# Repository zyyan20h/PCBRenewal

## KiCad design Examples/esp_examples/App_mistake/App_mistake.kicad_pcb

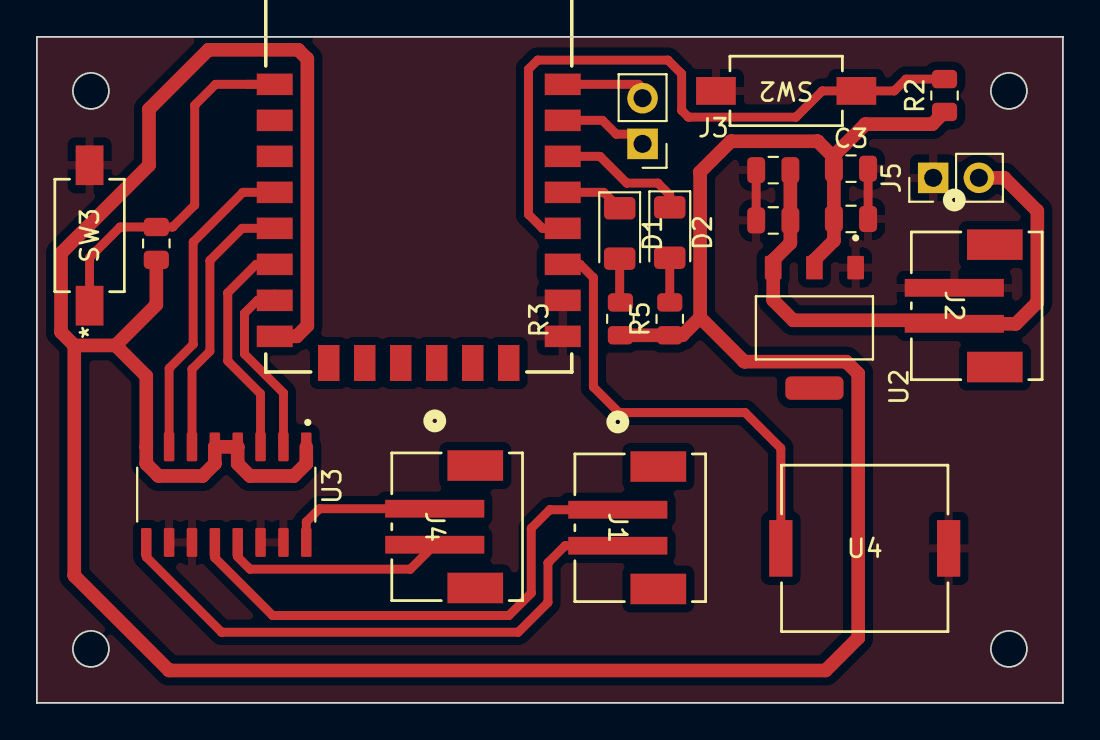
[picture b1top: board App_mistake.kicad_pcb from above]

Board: 2 copper layers, 57.0 x 37.0 mm, 21 parts (0 on the bottom side), 20 nets.

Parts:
C1, C2, C3, C4: C; C_0805_2012Metric
D1, D2: LED; LED_1206_3216Metric
J1, J2, J4: B2B-PH-SM4-TBLFSN; B2B-PH-SM4-TBLFSN_JST
J3, J5: Conn_01x02_Pin; PinHeader_1x02_P2.54mm_Vertical
R1, R2, R3, R5: R; R_0805_2012Metric
SW2, SW3: RS-282G05A3-SM RT; RS-282G05A3-SM RT_CNK
U1: ESP-12F
U2: AMS1117-3.3; SOT229P700X180-4N
U3: MX1508
U4: CPT-9019S-SMT-TR; SM_CPT_9X9_CUD

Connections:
/INL: J3.1, U1.21 (RXD)
/LED1: D1.1 (K), U1.19 (GPIO4)
/LED2: D2.1 (K), U1.20 (GPIO5)
/RST: R1.1, SW3.1, U1.1 (RST)
/VIN: C1.2, C2.2, J2.2, J5.2, U2.3 (VIN)
/boot: R2.2, SW2.1, U1.18 (GPIO0)
/buzzer: U1.17 (GPIO2), U4.1
/in1: U1.5 (GPIO14), U3.6 (INA2)
/in2: U1.4 (GPIO16), U3.7 (INB2)
/in3: U1.7 (GPIO13), U3.2 (INA1)
/in4: U1.6 (GPIO12), U3.3 (INB1)
GND: C1.1, C2.1, C3.2, C4.2, J2.1, J5.1, SW2.2, SW3.2, U1.15 (GND), U1.16 (GPIO15), U2.1 (GND/ADJ), U3.10 (AGND2), U3.11 (PGND2), U3.14 (AGND1), U3.15 (PGND1), U4.2
unnamed: D1.2 (A), R3.1
unnamed: D2.2 (A), R5.2
unnamed: J3.2, U1.22 (TXD)
unnamed: J4.1, U3.16 (OUTA1)
unnamed: J1.1, U3.12 (OUTA2)
unnamed: J4.2, U3.13 (OUTB1)
unnamed: J1.2, U3.9 (OUTB2)
VCC: C3.1, C4.1, R1.2, R2.1, R3.2, R5.1, U1.8 (VCC), U2.2 (VOUT), U3.1 (VCC1), U3.4 (VDD1), U3.5 (VCC2), U3.8 (VDD2)

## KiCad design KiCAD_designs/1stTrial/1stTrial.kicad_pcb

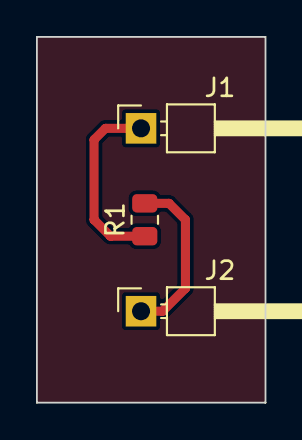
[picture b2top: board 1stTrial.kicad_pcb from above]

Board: 2 copper layers, 12.7 x 20.3 mm, 3 parts (0 on the bottom side), 2 nets.

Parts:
J1, J2: Conn_01x01_Pin; PinHeader_1x01_P2.54mm_Horizontal
R1: R; R_0805_2012Metric

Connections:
unnamed: J1.1, R1.1
unnamed: J2.1, R1.2

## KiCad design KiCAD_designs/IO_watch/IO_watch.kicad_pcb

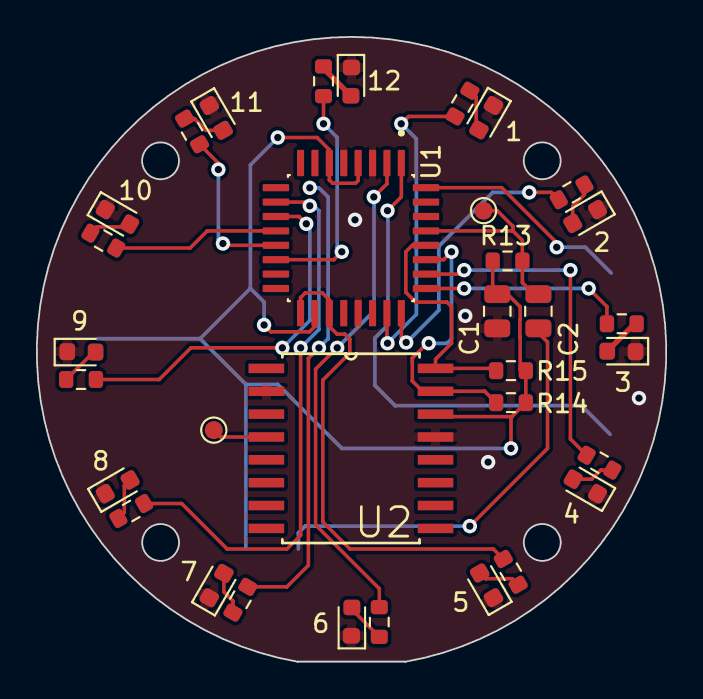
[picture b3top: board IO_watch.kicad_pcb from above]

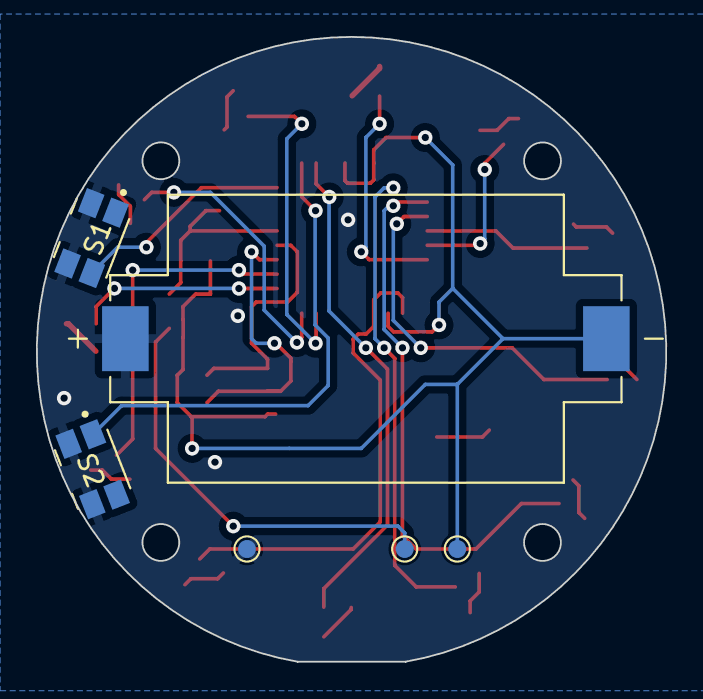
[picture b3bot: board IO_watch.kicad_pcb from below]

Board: 2 copper layers, 35.0 x 34.7 mm, 39 parts (6 on the bottom side), 33 nets.

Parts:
1, 2, 3, 4, 5, 12: LED; LED_0603_1608Metric
BT1: 1060TR; BAT_1060TR
C1: 1uF; C_0805_2012Metric
C2: 0.1uF; C_0805_2012Metric
D6, D7, D8, D9, D10, D11: LED; LED_0603_1608Metric
R1, R2, R3, R4, R5, R6, R7, R8, R9, R10, R11, R12: R; R_0603_1608Metric
R13, R14, R15: 10K; R_0603_1608Metric
S1, S2: EVQ-P7A01P; SW_EVQ-P7A01P
TP1, TP2, TP5, TP6, TP7: TestPoint; TestPoint_Pad_D1.0mm
U1: ATMEGA328P-AU; atmega328P_shinked
U2: DS3231S; DS3231

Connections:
/A0: R1.2, U1.23 (PC0)
/A1: R2.2, U1.24 (PC1)
/A2: R3.2, U1.25 (PC2)
/A3: R4.2, U1.26 (PC3)
/D2: S1.1_1, S1.1_2, U1.32 (PD2)
/D3: S2.1_1, S2.1_2, U1.1 (PD3)
/D4: R6.2, U1.2 (PD4)
/D5: R7.2, U1.9 (PD5)
/D6: R8.2, U1.10 (PD6)
/D7: R9.2, U1.11 (PD7)
/D8: R10.2, U1.12 (PB0)
/D9: R11.2, U1.13 (PB1)
/D10: R12.2, U1.14 (PB2)
/D13: R5.2, U1.17 (PB5), U1.19 (ADC6)
/D-: C2.2, TP2.1
/RST: C2.1, R13.1, TP7.1, U1.29 (PC6/~RESET)
/SCL: R15.1, U1.28 (PC5), U2.16 (SCL)
/SDA: R14.2, U1.27 (PC4), U2.15 (SDA)
GND: 1.1 (K), 2.1 (K), 3.1 (K), 4.1 (K), 5.1 (K), 12.1 (K), BT1.P, C1.2, D6.1 (K), D7.1 (K), D8.1 (K), D9.1 (K), D10.1 (K), D11.1 (K), S1.2_1, S1.2_2, S2.2_1, S2.2_2, TP5.1, U1.3 (GND), U1.5 (GND), U1.21 (GND), U2.2 (VCC), U2.13 (GND)
unnamed: 1.2 (A), R1.1
unnamed: 2.2 (A), R2.1
unnamed: 3.2 (A), R3.1
unnamed: 4.2 (A), R4.1
unnamed: 5.2 (A), R5.1
unnamed: D6.2 (A), R6.1
unnamed: D7.2 (A), R7.1
unnamed: D8.2 (A), R8.1
unnamed: D9.2 (A), R9.1
unnamed: D10.2 (A), R10.1
unnamed: D11.2 (A), R11.1
unnamed: 12.2 (A), R12.1
unnamed: TP6.1, U2.4 (~RST)
VCC: BT1.N, C1.1, R13.2, R14.1, R15.2, TP1.1, U1.4 (VCC), U1.6 (VCC), U1.18 (AVCC), U2.14 (VBAT)

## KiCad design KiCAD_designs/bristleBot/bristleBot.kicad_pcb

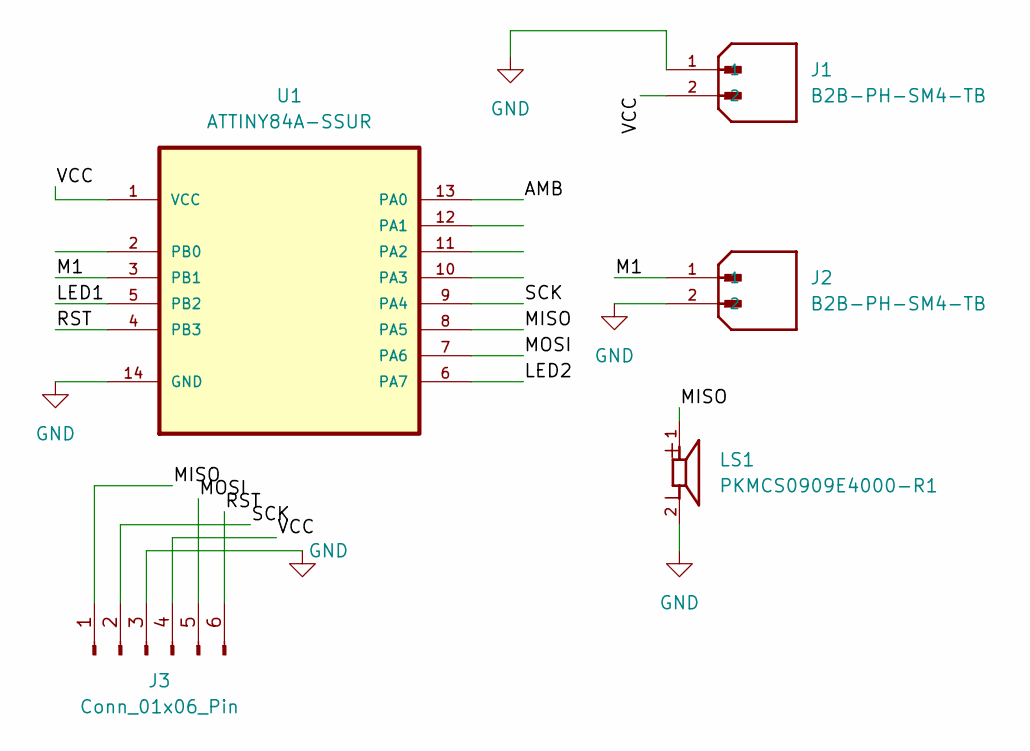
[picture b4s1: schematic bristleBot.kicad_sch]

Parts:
J1, J2: B2B-PH-SM4-TB; JST_B2B-PH-SM4-TB; PARTREV N/A
J3: Conn_01x06_Pin; PinHeader_1x06_P2.54mm_Horizontal
LS1: PKMCS0909E4000-R1; SPKR_PKMCS0909E4000-R1; PARTREV May 22, 2020
U1: ATTINY84A-SSUR; SOIC127P600X175-14N; MPN ATTINY84A-SSUR

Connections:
/AMB: U1.13 (PA0)
/LED1: U1.5 (PB2)
/LED2: U1.6 (PA7)
/M1: J2.1, U1.3 (PB1)
/MISO: J3.1, LS1.1, U1.8 (PA5)
/MOSI: J3.5, U1.7 (PA6)
/RST: J3.6, U1.4 (PB3)
/SCK: J3.2, U1.9 (PA4)
/VCC: J1.2, J3.4, U1.1 (VCC)
GND: J1.1, J2.2, J3.3, LS1.2, U1.14 (GND)

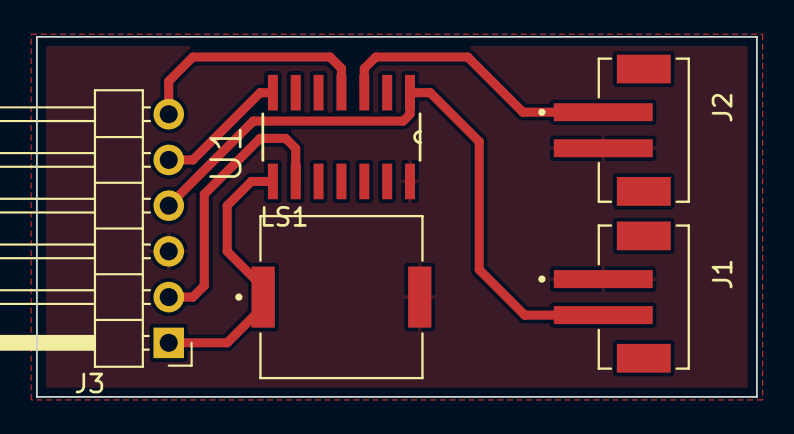
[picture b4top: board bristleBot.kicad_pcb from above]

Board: 2 copper layers, 40.0 x 20.0 mm, 5 parts (0 on the bottom side), 7 nets.
